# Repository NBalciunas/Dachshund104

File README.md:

# Dachshund104

P.S. I changed my github handle, the link in the picture is no longer valid.

## Features:
- Powered by Teensy++ 2.0
- ANSI 104 layout
- Full RGB
- Hot swappable
- 4 layer PCB
- South facing switches
- PCB mounted stabilizers

## Some information about the RGB functionality

All of the RGB controls are connecetd to 4 pins which you can either connect to the Teensy++ 2.0 or a seprete RGB controler

RGB is optional and if you are planning on not using it I would recommend to edit out the RGB leds and reroute to make a 2 layer PCB instead and save some money printing PCBs

## Pictures

# Honorable mention to this dachshund

Mindšunis (engl. Mindog)

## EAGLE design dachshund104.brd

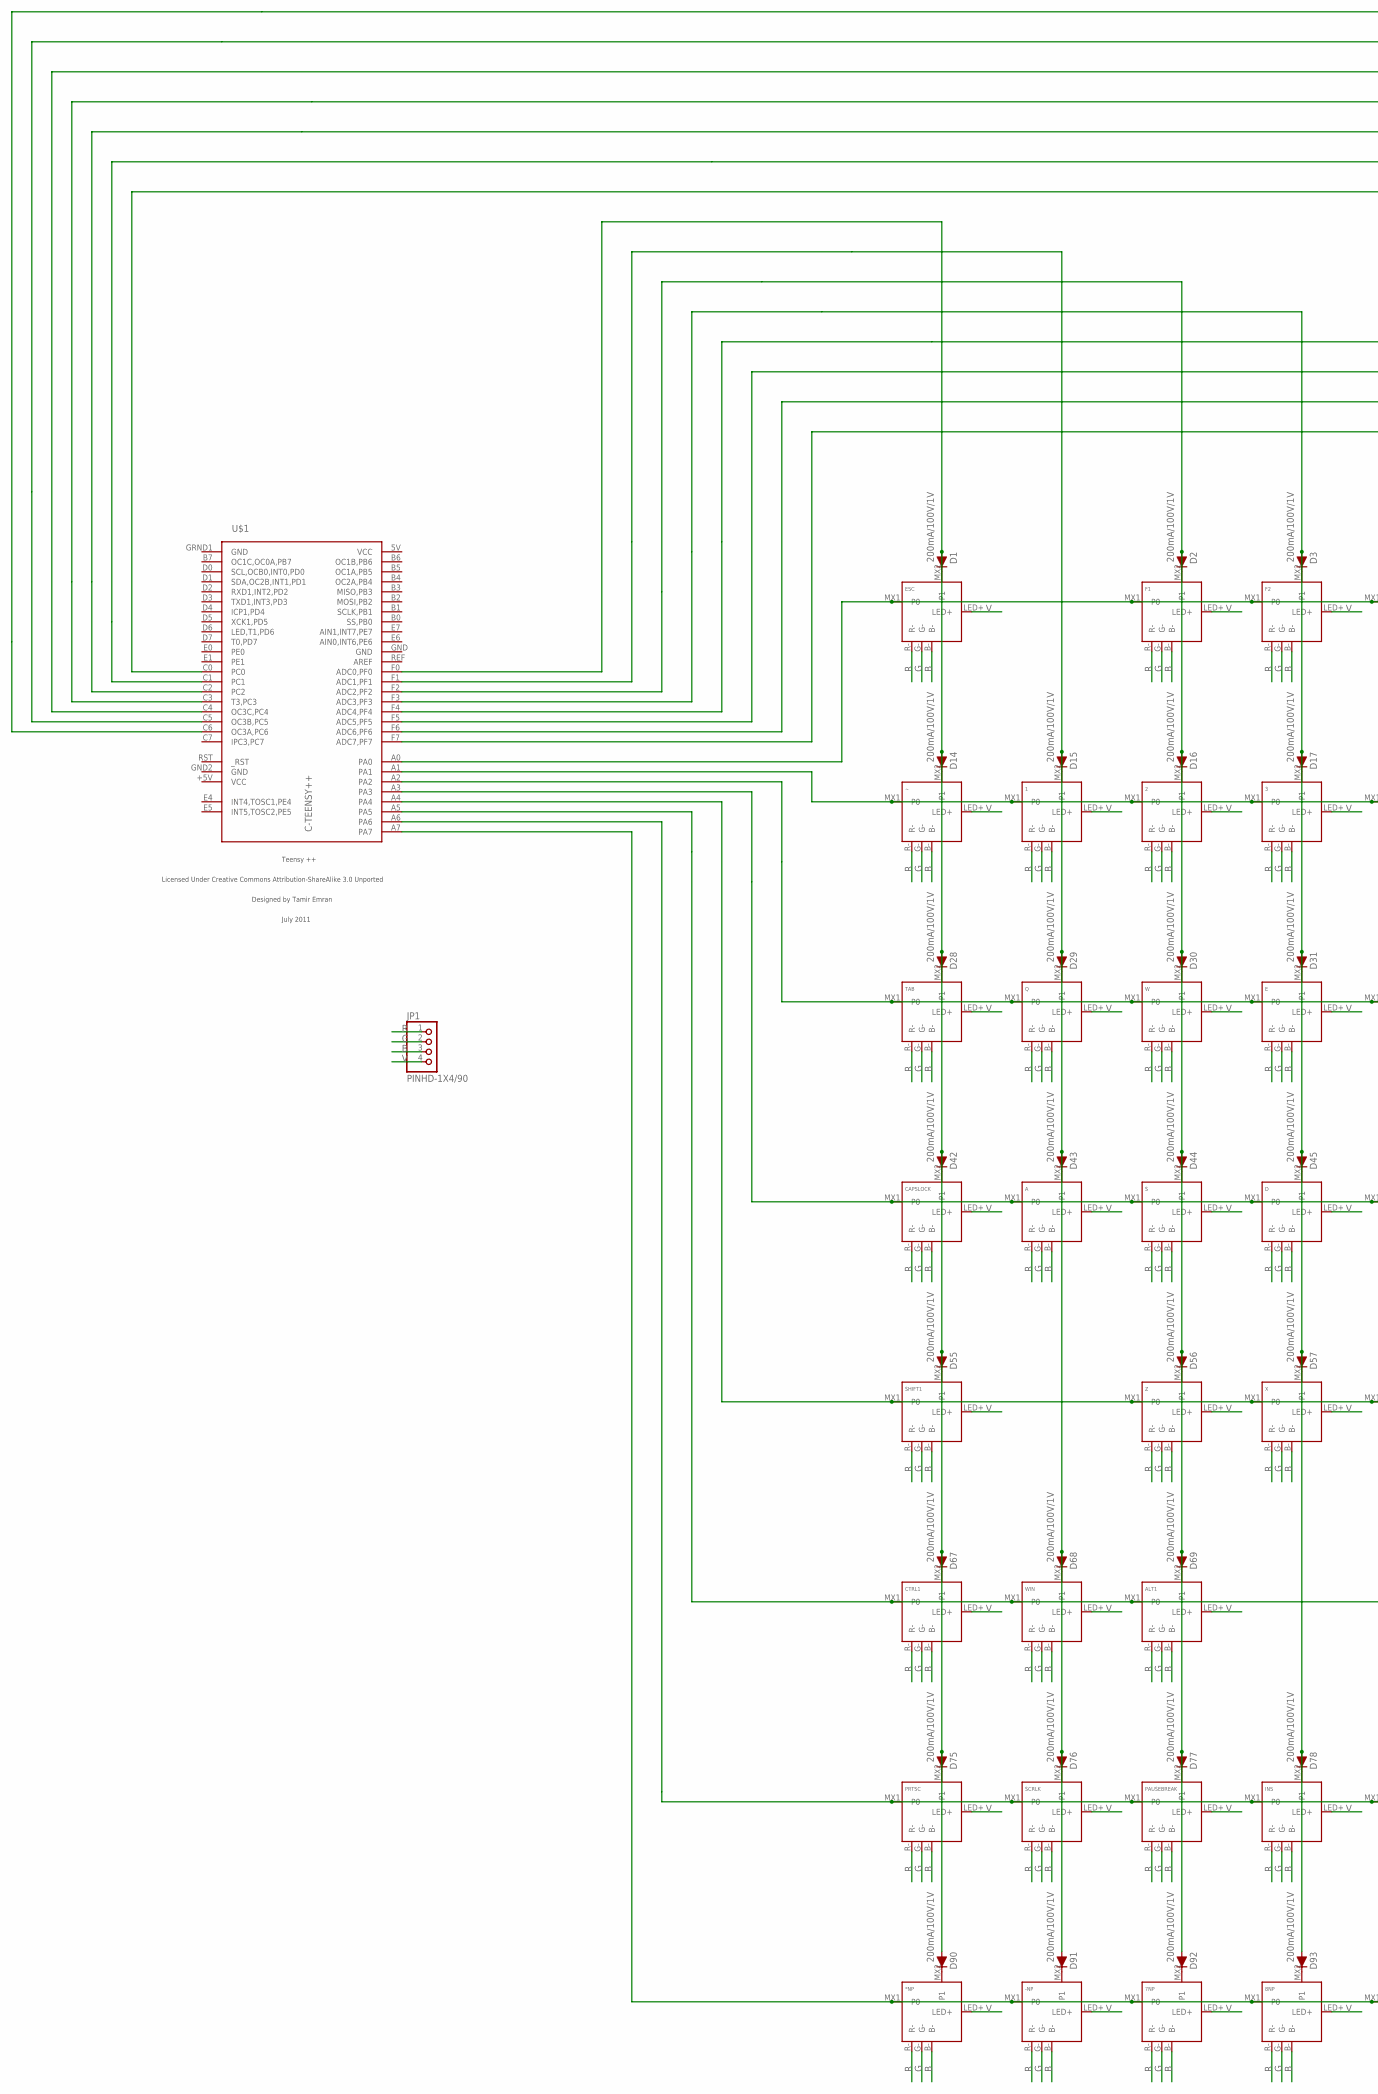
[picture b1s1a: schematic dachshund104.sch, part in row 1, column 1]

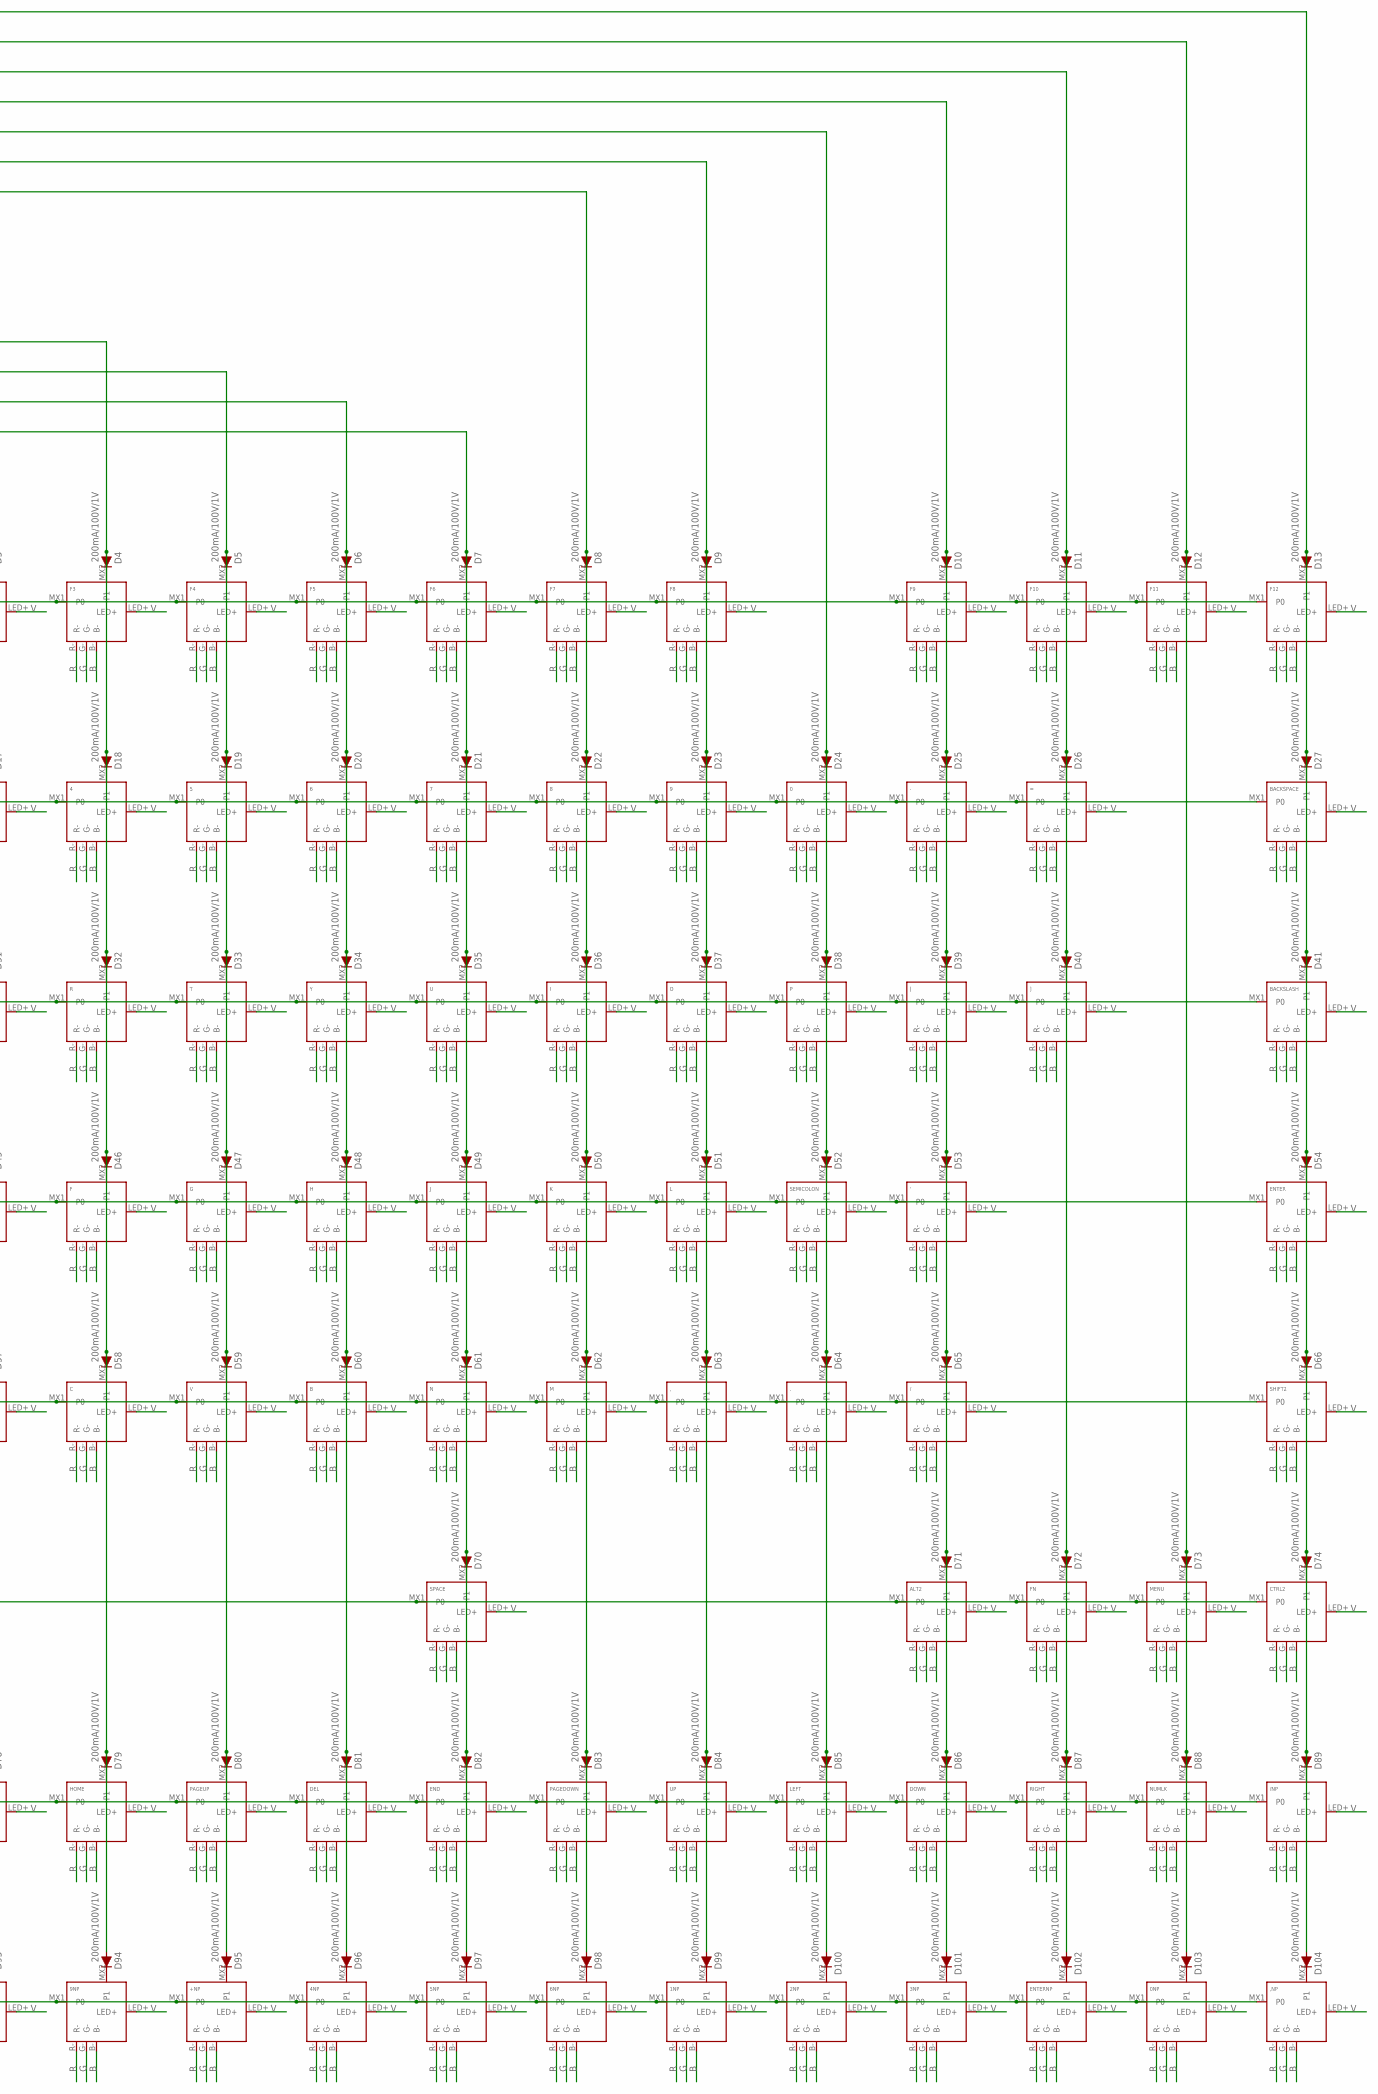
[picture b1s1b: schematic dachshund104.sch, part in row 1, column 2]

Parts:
0, 1, 1NP, 2, 2NP, 3, 3NP, 4, 4NP, 5, 5NP, 6, 6NP, 7, 7NP, 8, 8NP, 9, 9NP, .: KEYSWITCH-RGBSMDLED-MXHSPCB-1U-SMDRGB; MXHSPCB-1U-SMDRGB
0NP: KEYSWITCH-RGBSMDLED-MXHSPCB-2U-SMDRGB; MXHSPCB-2U-SMDRGB
': KEYSWITCH-RGBSMDLED-MXHSPCB-1U-SMDRGB; MXHSPCB-1U-SMDRGB
*NP: KEYSWITCH-RGBSMDLED-MXHSPCB-1U-SMDRGB; MXHSPCB-1U-SMDRGB
+NP: KEYSWITCH-RGBSMDLED-MXHSPCB-2U-SMDRGB-ROTATED; MXHSPCB-2U-SMDRGB-ROTATED
,: KEYSWITCH-RGBSMDLED-MXHSPCB-1U-SMDRGB; MXHSPCB-1U-SMDRGB
,NP: KEYSWITCH-RGBSMDLED-MXHSPCB-1U-SMDRGB; MXHSPCB-1U-SMDRGB
-: KEYSWITCH-RGBSMDLED-MXHSPCB-1U-SMDRGB; MXHSPCB-1U-SMDRGB
-NP: KEYSWITCH-RGBSMDLED-MXHSPCB-1U-SMDRGB; MXHSPCB-1U-SMDRGB
/: KEYSWITCH-RGBSMDLED-MXHSPCB-1U-SMDRGB; MXHSPCB-1U-SMDRGB
/NP: KEYSWITCH-RGBSMDLED-MXHSPCB-1U-SMDRGB; MXHSPCB-1U-SMDRGB
=: KEYSWITCH-RGBSMDLED-MXHSPCB-1U-SMDRGB; MXHSPCB-1U-SMDRGB
A: KEYSWITCH-RGBSMDLED-MXHSPCB-1U-SMDRGB; MXHSPCB-1U-SMDRGB
ALT1, ALT2: KEYSWITCH-RGBSMDLED-MXHSPCB-1U-SMDRGB; MXHSPCB-1U-SMDRGB
B: KEYSWITCH-RGBSMDLED-MXHSPCB-1U-SMDRGB; MXHSPCB-1U-SMDRGB
BACKSLASH: KEYSWITCH-RGBSMDLED-MXHSPCB-1U-SMDRGB; MXHSPCB-1U-SMDRGB
BACKSPACE: KEYSWITCH-RGBSMDLED-MXHSPCB-2U-SMDRGB; MXHSPCB-2U-SMDRGB
C: KEYSWITCH-RGBSMDLED-MXHSPCB-1U-SMDRGB; MXHSPCB-1U-SMDRGB
CAPSLOCK: KEYSWITCH-RGBSMDLED-MXHSPCB-1U-SMDRGB; MXHSPCB-1U-SMDRGB
CTRL1, CTRL2: KEYSWITCH-RGBSMDLED-MXHSPCB-1U-SMDRGB; MXHSPCB-1U-SMDRGB
D: KEYSWITCH-RGBSMDLED-MXHSPCB-1U-SMDRGB; MXHSPCB-1U-SMDRGB
D1, D2, D3, D4, D5, D6, D7, D8, D9, D10, D11, D12, D13, D14, D15, D16, D17, D18, D19, D20, D21, D22, D23, D24, D25, D26, D27, D28, D29, D30, D31, D32, D33, D34, D35, D36, D37, D38, D39, D40, D41, D42, D43, D44, D45, D46, D47, D48, D49, D50, D51, D52, D53, D54, D55, D56, D57, D58, D59, D60, D61, D62, D63, D64, D65, D66, D67, D68, D69, D70, D71, D72, D73, D74, D75, D76, D77, D78, D79, D80, D81, D82, D83, D84, D85, D86, D87, D88, D89, D90, D91, D92, D93, D94, D95, D96, D97, D98, D99, D100, D101, D102, D103, D104: 200mA/100V/1V; DIODE-1N4148
DEL: KEYSWITCH-RGBSMDLED-MXHSPCB-1U-SMDRGB; MXHSPCB-1U-SMDRGB
DOWN: KEYSWITCH-RGBSMDLED-MXHSPCB-1U-SMDRGB; MXHSPCB-1U-SMDRGB
E: KEYSWITCH-RGBSMDLED-MXHSPCB-1U-SMDRGB; MXHSPCB-1U-SMDRGB
END: KEYSWITCH-RGBSMDLED-MXHSPCB-1U-SMDRGB; MXHSPCB-1U-SMDRGB
ENTER: KEYSWITCH-RGBSMDLED-MXHSPCB-2U-SMDRGB; MXHSPCB-2U-SMDRGB
ENTERNP: KEYSWITCH-RGBSMDLED-MXHSPCB-2U-SMDRGB-ROTATED; MXHSPCB-2U-SMDRGB-ROTATED
ESC: KEYSWITCH-RGBSMDLED-MXHSPCB-1U-SMDRGB; MXHSPCB-1U-SMDRGB
F, F1, F2, F3, F4, F5, F6, F7, F8, F9, F10, F11, F12: KEYSWITCH-RGBSMDLED-MXHSPCB-1U-SMDRGB; MXHSPCB-1U-SMDRGB
FN: KEYSWITCH-RGBSMDLED-MXHSPCB-1U-SMDRGB; MXHSPCB-1U-SMDRGB
G: KEYSWITCH-RGBSMDLED-MXHSPCB-1U-SMDRGB; MXHSPCB-1U-SMDRGB
H: KEYSWITCH-RGBSMDLED-MXHSPCB-1U-SMDRGB; MXHSPCB-1U-SMDRGB
HOME: KEYSWITCH-RGBSMDLED-MXHSPCB-1U-SMDRGB; MXHSPCB-1U-SMDRGB
I: KEYSWITCH-RGBSMDLED-MXHSPCB-1U-SMDRGB; MXHSPCB-1U-SMDRGB
INS: KEYSWITCH-RGBSMDLED-MXHSPCB-1U-SMDRGB; MXHSPCB-1U-SMDRGB
J: KEYSWITCH-RGBSMDLED-MXHSPCB-1U-SMDRGB; MXHSPCB-1U-SMDRGB
JP1: PINHD-1X4/90; 1X04/90
K: KEYSWITCH-RGBSMDLED-MXHSPCB-1U-SMDRGB; MXHSPCB-1U-SMDRGB
L: KEYSWITCH-RGBSMDLED-MXHSPCB-1U-SMDRGB; MXHSPCB-1U-SMDRGB
LEFT: KEYSWITCH-RGBSMDLED-MXHSPCB-1U-SMDRGB; MXHSPCB-1U-SMDRGB
M: KEYSWITCH-RGBSMDLED-MXHSPCB-1U-SMDRGB; MXHSPCB-1U-SMDRGB
MENU: KEYSWITCH-RGBSMDLED-MXHSPCB-1U-SMDRGB; MXHSPCB-1U-SMDRGB
N: KEYSWITCH-RGBSMDLED-MXHSPCB-1U-SMDRGB; MXHSPCB-1U-SMDRGB
NUMLK: KEYSWITCH-RGBSMDLED-MXHSPCB-1U-SMDRGB; MXHSPCB-1U-SMDRGB
O: KEYSWITCH-RGBSMDLED-MXHSPCB-1U-SMDRGB; MXHSPCB-1U-SMDRGB
P: KEYSWITCH-RGBSMDLED-MXHSPCB-1U-SMDRGB; MXHSPCB-1U-SMDRGB
PAGEDOWN: KEYSWITCH-RGBSMDLED-MXHSPCB-1U-SMDRGB; MXHSPCB-1U-SMDRGB
PAGEUP: KEYSWITCH-RGBSMDLED-MXHSPCB-1U-SMDRGB; MXHSPCB-1U-SMDRGB
PAUSEBREAK: KEYSWITCH-RGBSMDLED-MXHSPCB-1U-SMDRGB; MXHSPCB-1U-SMDRGB
PRTSC: KEYSWITCH-RGBSMDLED-MXHSPCB-1U-SMDRGB; MXHSPCB-1U-SMDRGB
Q: KEYSWITCH-RGBSMDLED-MXHSPCB-1U-SMDRGB; MXHSPCB-1U-SMDRGB
R: KEYSWITCH-RGBSMDLED-MXHSPCB-1U-SMDRGB; MXHSPCB-1U-SMDRGB
RIGHT: KEYSWITCH-RGBSMDLED-MXHSPCB-1U-SMDRGB; MXHSPCB-1U-SMDRGB
S: KEYSWITCH-RGBSMDLED-MXHSPCB-1U-SMDRGB; MXHSPCB-1U-SMDRGB
SCRLK: KEYSWITCH-RGBSMDLED-MXHSPCB-1U-SMDRGB; MXHSPCB-1U-SMDRGB
SEMICOLON: KEYSWITCH-RGBSMDLED-MXHSPCB-1U-SMDRGB; MXHSPCB-1U-SMDRGB
SHIFT1, SHIFT2: KEYSWITCH-RGBSMDLED-MXHSPCB-2U-SMDRGB; MXHSPCB-2U-SMDRGB
SPACE: KEYSWITCH-RGBSMDLED-MXHSPCB-6.25U-SMDRGB; MXHSPCB-6.25U-SMDRGB
T: KEYSWITCH-RGBSMDLED-MXHSPCB-1U-SMDRGB; MXHSPCB-1U-SMDRGB
TAB: KEYSWITCH-RGBSMDLED-MXHSPCB-1U-SMDRGB; MXHSPCB-1U-SMDRGB
U: KEYSWITCH-RGBSMDLED-MXHSPCB-1U-SMDRGB; MXHSPCB-1U-SMDRGB
U$1: C-TEENSY++; TEENSY++
UP: KEYSWITCH-RGBSMDLED-MXHSPCB-1U-SMDRGB; MXHSPCB-1U-SMDRGB
V: KEYSWITCH-RGBSMDLED-MXHSPCB-1U-SMDRGB; MXHSPCB-1U-SMDRGB
W: KEYSWITCH-RGBSMDLED-MXHSPCB-1U-SMDRGB; MXHSPCB-1U-SMDRGB
WIN: KEYSWITCH-RGBSMDLED-MXHSPCB-1U-SMDRGB; MXHSPCB-1U-SMDRGB
X: KEYSWITCH-RGBSMDLED-MXHSPCB-1U-SMDRGB; MXHSPCB-1U-SMDRGB
Y: KEYSWITCH-RGBSMDLED-MXHSPCB-1U-SMDRGB; MXHSPCB-1U-SMDRGB
Z: KEYSWITCH-RGBSMDLED-MXHSPCB-1U-SMDRGB; MXHSPCB-1U-SMDRGB
[: KEYSWITCH-RGBSMDLED-MXHSPCB-1U-SMDRGB; MXHSPCB-1U-SMDRGB
]: KEYSWITCH-RGBSMDLED-MXHSPCB-1U-SMDRGB; MXHSPCB-1U-SMDRGB
~: KEYSWITCH-RGBSMDLED-MXHSPCB-1U-SMDRGB; MXHSPCB-1U-SMDRGB

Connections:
B: 0.B-, 0NP.B-, 1.B-, 1NP.B-, 2.B-, 2NP.B-, 3.B-, 3NP.B-, 4.B-, 4NP.B-, 5.B-, 5NP.B-, 6.B-, 6NP.B-, 7.B-, 7NP.B-, 8.B-, 8NP.B-, 9.B-, 9NP.B-, '.B-, *NP.B-, +NP.B-, ,.B-, ,NP.B-, -.B-, -NP.B-, ..B-, /.B-, /NP.B-, =.B-, A.B-, ALT1.B-, ALT2.B-, B.B-, BACKSLASH.B-, BACKSPACE.B-, C.B-, CAPSLOCK.B-, CTRL1.B-, CTRL2.B-, D.B-, DEL.B-, DOWN.B-, E.B-, END.B-, ENTER.B-, ENTERNP.B-, ESC.B-, F.B-, F1.B-, F2.B-, F3.B-, F4.B-, F5.B-, F6.B-, F7.B-, F8.B-, F9.B-, F10.B-, F11.B-, F12.B-, FN.B-, G.B-, H.B-, HOME.B-, I.B-, INS.B-, J.B-, JP1.3, K.B-, L.B-, LEFT.B-, M.B-, MENU.B-, N.B-, NUMLK.B-, O.B-, P.B-, PAGEDOWN.B-, PAGEUP.B-, PAUSEBREAK.B-, PRTSC.B-, Q.B-, R.B-, RIGHT.B-, S.B-, SCRLK.B-, SEMICOLON.B-, SHIFT1.B-, SHIFT2.B-, SPACE.B-, T.B-, TAB.B-, U.B-, UP.B-, V.B-, W.B-, WIN.B-, X.B-, Y.B-, Z.B-, [.B-, ].B-, ~.B-
G: 0.G-, 0NP.G-, 1.G-, 1NP.G-, 2.G-, 2NP.G-, 3.G-, 3NP.G-, 4.G-, 4NP.G-, 5.G-, 5NP.G-, 6.G-, 6NP.G-, 7.G-, 7NP.G-, 8.G-, 8NP.G-, 9.G-, 9NP.G-, '.G-, *NP.G-, +NP.G-, ,.G-, ,NP.G-, -.G-, -NP.G-, ..G-, /.G-, /NP.G-, =.G-, A.G-, ALT1.G-, ALT2.G-, B.G-, BACKSLASH.G-, BACKSPACE.G-, C.G-, CAPSLOCK.G-, CTRL1.G-, CTRL2.G-, D.G-, DEL.G-, DOWN.G-, E.G-, END.G-, ENTER.G-, ENTERNP.G-, ESC.G-, F.G-, F1.G-, F2.G-, F3.G-, F4.G-, F5.G-, F6.G-, F7.G-, F8.G-, F9.G-, F10.G-, F11.G-, F12.G-, FN.G-, G.G-, H.G-, HOME.G-, I.G-, INS.G-, J.G-, JP1.2, K.G-, L.G-, LEFT.G-, M.G-, MENU.G-, N.G-, NUMLK.G-, O.G-, P.G-, PAGEDOWN.G-, PAGEUP.G-, PAUSEBREAK.G-, PRTSC.G-, Q.G-, R.G-, RIGHT.G-, S.G-, SCRLK.G-, SEMICOLON.G-, SHIFT1.G-, SHIFT2.G-, SPACE.G-, T.G-, TAB.G-, U.G-, UP.G-, V.G-, W.G-, WIN.G-, X.G-, Y.G-, Z.G-, [.G-, ].G-, ~.G-
GND: U$1.GND, U$1.GND2 (GND), U$1.GRND1 (GND)
unnamed: D1.C, ESC.MX2 (P1)
unnamed: BACKSPACE.MX2 (P1), D27.C
unnamed: D2.C, F1.MX2 (P1)
unnamed: D3.C, F2.MX2 (P1)
unnamed: D4.C, F3.MX2 (P1)
unnamed: D5.C, F4.MX2 (P1)
unnamed: D6.C, F5.MX2 (P1)
unnamed: D7.C, F6.MX2 (P1)
unnamed: D8.C, F7.MX2 (P1)
unnamed: D9.C, F8.MX2 (P1)
unnamed: D54.C, ENTER.MX2 (P1)
unnamed: D10.C, F9.MX2 (P1)
unnamed: D11.C, F10.MX2 (P1)
unnamed: D12.C, F11.MX2 (P1)
unnamed: D13.C, F12.MX2 (P1)
unnamed: D14.C, ~.MX2 (P1)
unnamed: 1.MX2 (P1), D15.C
unnamed: 2.MX2 (P1), D16.C
unnamed: 3.MX2 (P1), D17.C
unnamed: 4.MX2 (P1), D18.C
unnamed: 5.MX2 (P1), D19.C
unnamed: 6.MX2 (P1), D20.C
unnamed: 7.MX2 (P1), D21.C
unnamed: 8.MX2 (P1), D22.C
unnamed: 9.MX2 (P1), D23.C
unnamed: 0.MX2 (P1), D24.C
unnamed: -.MX2 (P1), D25.C
unnamed: BACKSLASH.MX2 (P1), D41.C
unnamed: D55.C, SHIFT1.MX2 (P1)
unnamed: D28.C, TAB.MX2 (P1)
unnamed: D29.C, Q.MX2 (P1)
unnamed: D30.C, W.MX2 (P1)
unnamed: D31.C, E.MX2 (P1)
unnamed: D32.C, R.MX2 (P1)
unnamed: D33.C, T.MX2 (P1)
unnamed: D34.C, Y.MX2 (P1)
unnamed: D35.C, U.MX2 (P1)
unnamed: D36.C, I.MX2 (P1)
unnamed: D37.C, O.MX2 (P1)
unnamed: D38.C, P.MX2 (P1)
unnamed: D39.C, [.MX2 (P1)
unnamed: D40.C, ].MX2 (P1)
unnamed: D66.C, SHIFT2.MX2 (P1)
unnamed: D70.C, SPACE.MX2 (P1)
unnamed: CAPSLOCK.MX2 (P1), D42.C
unnamed: A.MX2 (P1), D43.C
unnamed: D44.C, S.MX2 (P1)
unnamed: D.MX2 (P1), D45.C
unnamed: D46.C, F.MX2 (P1)
unnamed: D47.C, G.MX2 (P1)
unnamed: D48.C, H.MX2 (P1)
unnamed: D49.C, J.MX2 (P1)
unnamed: D50.C, K.MX2 (P1)
unnamed: D51.C, L.MX2 (P1)
unnamed: D52.C, SEMICOLON.MX2 (P1)
unnamed: '.MX2 (P1), D53.C
unnamed: D5.A, D19.A, D33.A, D47.A, D59.A, D80.A, D95.A, U$1.F5 (ADC5,PF5)
unnamed: D102.C, ENTERNP.MX2 (P1)
unnamed: 0NP.MX2 (P1), D103.C
unnamed: +NP.MX2 (P1), D95.C
unnamed: =.MX2 (P1), D26.C
unnamed: D56.C, Z.MX2 (P1)
unnamed: D57.C, X.MX2 (P1)
unnamed: C.MX2 (P1), D58.C
unnamed: D59.C, V.MX2 (P1)
unnamed: B.MX2 (P1), D60.C
unnamed: D61.C, N.MX2 (P1)
unnamed: D62.C, M.MX2 (P1)
unnamed: ,.MX2 (P1), D63.C
unnamed: ..MX2 (P1), D64.C
unnamed: /.MX2 (P1), D65.C
unnamed: D2.A, D16.A, D30.A, D44.A, D56.A, D69.A, D77.A, D92.A, U$1.F2 (ADC2,PF2)
unnamed: ESC.MX1 (P0), F1.MX1 (P0), F2.MX1 (P0), F3.MX1 (P0), F4.MX1 (P0), F5.MX1 (P0), F6.MX1 (P0), F7.MX1 (P0), F8.MX1 (P0), F9.MX1 (P0), F10.MX1 (P0), F11.MX1 (P0), F12.MX1 (P0), U$1.A0
unnamed: 0.MX1 (P0), 1.MX1 (P0), 2.MX1 (P0), 3.MX1 (P0), 4.MX1 (P0), 5.MX1 (P0), 6.MX1 (P0), 7.MX1 (P0), 8.MX1 (P0), 9.MX1 (P0), -.MX1 (P0), =.MX1 (P0), BACKSPACE.MX1 (P0), U$1.A1, ~.MX1 (P0)
unnamed: CTRL1.MX2 (P1), D67.C
unnamed: D68.C, WIN.MX2 (P1)
unnamed: ALT1.MX2 (P1), D69.C
unnamed: BACKSLASH.MX1 (P0), E.MX1 (P0), I.MX1 (P0), O.MX1 (P0), P.MX1 (P0), Q.MX1 (P0), R.MX1 (P0), T.MX1 (P0), TAB.MX1 (P0), U.MX1 (P0), U$1.A2, W.MX1 (P0), Y.MX1 (P0), [.MX1 (P0), ].MX1 (P0)
unnamed: '.MX1 (P0), A.MX1 (P0), CAPSLOCK.MX1 (P0), D.MX1 (P0), ENTER.MX1 (P0), F.MX1 (P0), G.MX1 (P0), H.MX1 (P0), J.MX1 (P0), K.MX1 (P0), L.MX1 (P0), S.MX1 (P0), SEMICOLON.MX1 (P0), U$1.A3
unnamed: ,.MX1 (P0), ..MX1 (P0), /.MX1 (P0), B.MX1 (P0), C.MX1 (P0), M.MX1 (P0), N.MX1 (P0), SHIFT1.MX1 (P0), SHIFT2.MX1 (P0), U$1.A4, V.MX1 (P0), X.MX1 (P0), Z.MX1 (P0)
unnamed: ALT1.MX1 (P0), ALT2.MX1 (P0), CTRL1.MX1 (P0), CTRL2.MX1 (P0), FN.MX1 (P0), MENU.MX1 (P0), SPACE.MX1 (P0), U$1.A5, WIN.MX1 (P0)
unnamed: /NP.MX1 (P0), DEL.MX1 (P0), DOWN.MX1 (P0), END.MX1 (P0), HOME.MX1 (P0), INS.MX1 (P0), LEFT.MX1 (P0), NUMLK.MX1 (P0), PAGEDOWN.MX1 (P0), PAGEUP.MX1 (P0), PAUSEBREAK.MX1 (P0), PRTSC.MX1 (P0), RIGHT.MX1 (P0), SCRLK.MX1 (P0), U$1.A6, UP.MX1 (P0)
unnamed: 0NP.MX1 (P0), 1NP.MX1 (P0), 2NP.MX1 (P0), 3NP.MX1 (P0), 4NP.MX1 (P0), 5NP.MX1 (P0), 6NP.MX1 (P0), 7NP.MX1 (P0), 8NP.MX1 (P0), 9NP.MX1 (P0), *NP.MX1 (P0), +NP.MX1 (P0), ,NP.MX1 (P0), -NP.MX1 (P0), ENTERNP.MX1 (P0), U$1.A7
unnamed: ALT2.MX2 (P1), D71.C
unnamed: D72.C, FN.MX2 (P1)
unnamed: D1.A, D14.A, D28.A, D42.A, D55.A, D67.A, D75.A, D90.A, U$1.F0 (ADC0,PF0)
unnamed: D15.A, D29.A, D43.A, D68.A, D76.A, D91.A, U$1.F1 (ADC1,PF1)
unnamed: D73.C, MENU.MX2 (P1)
unnamed: CTRL2.MX2 (P1), D74.C
unnamed: D75.C, PRTSC.MX2 (P1)
unnamed: D76.C, SCRLK.MX2 (P1)
unnamed: D77.C, PAUSEBREAK.MX2 (P1)
unnamed: D78.C, INS.MX2 (P1)
unnamed: D79.C, HOME.MX2 (P1)
unnamed: D80.C, PAGEUP.MX2 (P1)
unnamed: D81.C, DEL.MX2 (P1)
unnamed: D82.C, END.MX2 (P1)
unnamed: D83.C, PAGEDOWN.MX2 (P1)
unnamed: D84.C, UP.MX2 (P1)
unnamed: D85.C, LEFT.MX2 (P1)
unnamed: D86.C, DOWN.MX2 (P1)
unnamed: D87.C, RIGHT.MX2 (P1)
unnamed: D88.C, NUMLK.MX2 (P1)
unnamed: /NP.MX2 (P1), D89.C
unnamed: *NP.MX2 (P1), D90.C
unnamed: -NP.MX2 (P1), D91.C
unnamed: 7NP.MX2 (P1), D92.C
unnamed: 8NP.MX2 (P1), D93.C
unnamed: 9NP.MX2 (P1), D94.C
unnamed: 4NP.MX2 (P1), D96.C
unnamed: 5NP.MX2 (P1), D97.C
unnamed: 6NP.MX2 (P1), D98.C
unnamed: 1NP.MX2 (P1), D99.C
unnamed: 2NP.MX2 (P1), D100.C
unnamed: 3NP.MX2 (P1), D101.C
unnamed: D3.A, D17.A, D31.A, D45.A, D57.A, D78.A, D93.A, U$1.F3 (ADC3,PF3)
unnamed: ,NP.MX2 (P1), D104.C
unnamed: D4.A, D18.A, D32.A, D46.A, D58.A, D79.A, D94.A, U$1.F4 (ADC4,PF4)
unnamed: D6.A, D20.A, D34.A, D48.A, D60.A, D81.A, D96.A, U$1.F6 (ADC6,PF6)
unnamed: D7.A, D21.A, D35.A, D49.A, D61.A, D70.A, D82.A, D97.A, U$1.F7 (ADC7,PF7)
unnamed: D9.A, D23.A, D37.A, D51.A, D63.A, D84.A, D99.A, U$1.C1
unnamed: D24.A, D38.A, D52.A, D64.A, D85.A, D100.A, U$1.C2
unnamed: D10.A, D25.A, D39.A, D53.A, D65.A, D71.A, D86.A, D101.A, U$1.C3 (T3,PC3)
unnamed: D11.A, D26.A, D40.A, D72.A, D87.A, D102.A, U$1.C4 (OC3C,PC4)
unnamed: D12.A, D73.A, D88.A, D103.A, U$1.C5 (OC3B,PC5)
unnamed: D13.A, D27.A, D41.A, D54.A, D66.A, D74.A, D89.A, D104.A, U$1.C6 (OC3A,PC6)
unnamed: D8.A, D22.A, D36.A, D50.A, D62.A, D83.A, D98.A, U$1.C0
R: 0.R-, 0NP.R-, 1.R-, 1NP.R-, 2.R-, 2NP.R-, 3.R-, 3NP.R-, 4.R-, 4NP.R-, 5.R-, 5NP.R-, 6.R-, 6NP.R-, 7.R-, 7NP.R-, 8.R-, 8NP.R-, 9.R-, 9NP.R-, '.R-, *NP.R-, +NP.R-, ,.R-, ,NP.R-, -.R-, -NP.R-, ..R-, /.R-, /NP.R-, =.R-, A.R-, ALT1.R-, ALT2.R-, B.R-, BACKSLASH.R-, BACKSPACE.R-, C.R-, CAPSLOCK.R-, CTRL1.R-, CTRL2.R-, D.R-, DEL.R-, DOWN.R-, E.R-, END.R-, ENTER.R-, ENTERNP.R-, ESC.R-, F.R-, F1.R-, F2.R-, F3.R-, F4.R-, F5.R-, F6.R-, F7.R-, F8.R-, F9.R-, F10.R-, F11.R-, F12.R-, FN.R-, G.R-, H.R-, HOME.R-, I.R-, INS.R-, J.R-, JP1.1, K.R-, L.R-, LEFT.R-, M.R-, MENU.R-, N.R-, NUMLK.R-, O.R-, P.R-, PAGEDOWN.R-, PAGEUP.R-, PAUSEBREAK.R-, PRTSC.R-, Q.R-, R.R-, RIGHT.R-, S.R-, SCRLK.R-, SEMICOLON.R-, SHIFT1.R-, SHIFT2.R-, SPACE.R-, T.R-, TAB.R-, U.R-, UP.R-, V.R-, W.R-, WIN.R-, X.R-, Y.R-, Z.R-, [.R-, ].R-, ~.R-
V: 0.LED+, 0NP.LED+, 1.LED+, 1NP.LED+, 2.LED+, 2NP.LED+, 3.LED+, 3NP.LED+, 4.LED+, 4NP.LED+, 5.LED+, 5NP.LED+, 6.LED+, 6NP.LED+, 7.LED+, 7NP.LED+, 8.LED+, 8NP.LED+, 9.LED+, 9NP.LED+, '.LED+, *NP.LED+, +NP.LED+, ,.LED+, ,NP.LED+, -.LED+, -NP.LED+, ..LED+, /.LED+, /NP.LED+, =.LED+, A.LED+, ALT1.LED+, ALT2.LED+, B.LED+, BACKSLASH.LED+, BACKSPACE.LED+, C.LED+, CAPSLOCK.LED+, CTRL1.LED+, CTRL2.LED+, D.LED+, DEL.LED+, DOWN.LED+, E.LED+, END.LED+, ENTER.LED+, ENTERNP.LED+, ESC.LED+, F.LED+, F1.LED+, F2.LED+, F3.LED+, F4.LED+, F5.LED+, F6.LED+, F7.LED+, F8.LED+, F9.LED+, F10.LED+, F11.LED+, F12.LED+, FN.LED+, G.LED+, H.LED+, HOME.LED+, I.LED+, INS.LED+, J.LED+, JP1.4, K.LED+, L.LED+, LEFT.LED+, M.LED+, MENU.LED+, N.LED+, NUMLK.LED+, O.LED+, P.LED+, PAGEDOWN.LED+, PAGEUP.LED+, PAUSEBREAK.LED+, PRTSC.LED+, Q.LED+, R.LED+, RIGHT.LED+, S.LED+, SCRLK.LED+, SEMICOLON.LED+, SHIFT1.LED+, SHIFT2.LED+, SPACE.LED+, T.LED+, TAB.LED+, U.LED+, UP.LED+, V.LED+, W.LED+, WIN.LED+, X.LED+, Y.LED+, Z.LED+, [.LED+, ].LED+, ~.LED+
VCC: U$1.5V (VCC), U$1.+5V (VCC)

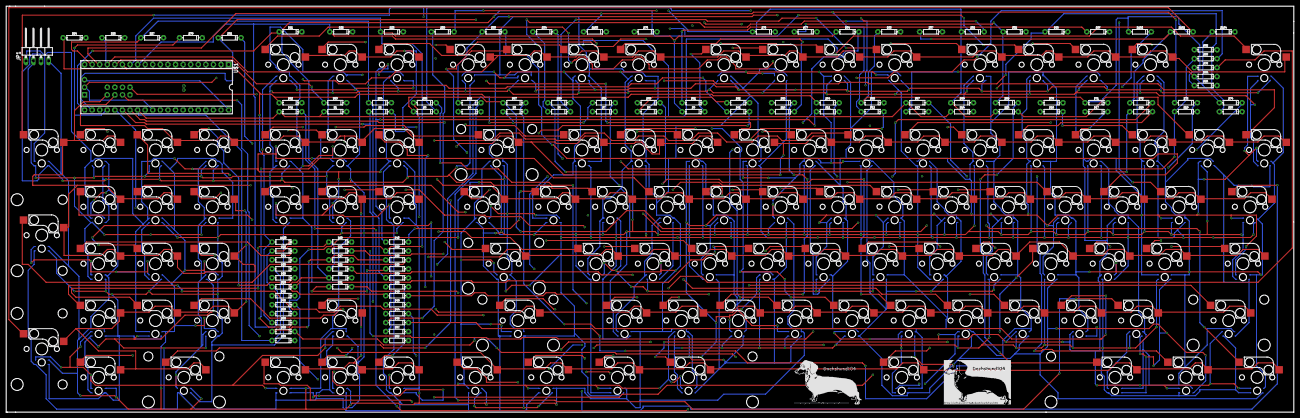
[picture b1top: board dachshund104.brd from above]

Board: 4 copper layers, 431.4 x 136.0 mm, 210 parts (0 on the bottom side), 133 nets.

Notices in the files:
parts and their libraries:
SparkFun-DiscreteSemi: Licensing: Creative Commons ShareAlike 4.0 International - https://creativecommons.org/licenses/by-sa/4.0
teensypp: Licensed Under Creative Commons
teensypp: Licensed Under Creative Commons Attribution-ShareAlike 3.0 Unported
